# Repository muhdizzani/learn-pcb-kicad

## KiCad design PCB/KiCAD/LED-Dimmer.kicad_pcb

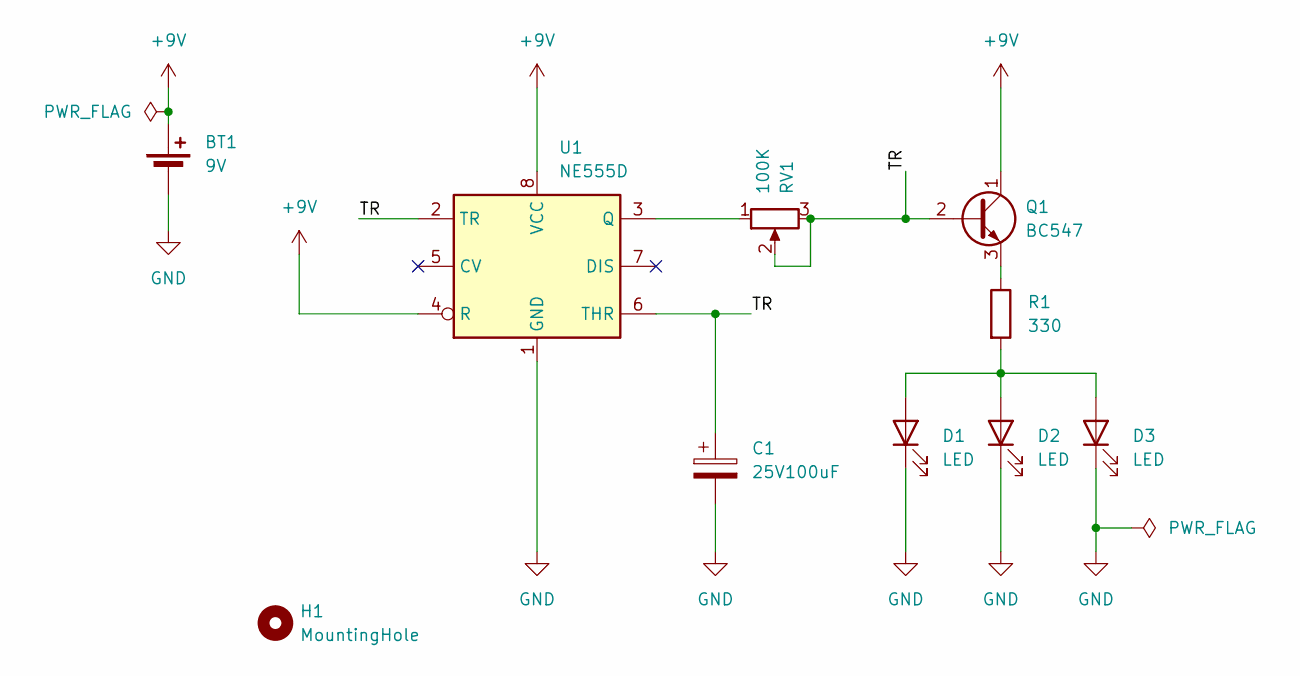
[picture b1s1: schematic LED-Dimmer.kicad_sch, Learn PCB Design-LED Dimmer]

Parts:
BT1: 9V; TerminalBlock_Phoenix_MKDS-1,5-2-5.08_1x02_P5.08mm_Horizont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
C1: 25V100uF; CP_Radial_D5.0mm_P2.00mm
D1, D2, D3: LED; LED_D5.0mm_Clear
H1: MountingHole; MountingHole_2.1mm
Q1: BC547; TO-92
R1: 330; R_Axial_DIN0204_L3.6mm_D1.6mm_P7.62mm_Horizontal
RV1: 100K; Potentiometer_Bourns_3296Y_Vertical
U1: NE555D; SOIC-8_3.9x4.9mm_P1.27mm

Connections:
+9V: BT1.1 (+), Q1.1 (C), U1.4 (R), U1.8 (VCC)
/TR: C1.1, Q1.2 (B), RV1.2, RV1.3, U1.2 (TR), U1.6 (THR)
GND: BT1.2 (-), C1.2, D1.1 (K), D2.1 (K), D3.1 (K), U1.1 (GND)
unnamed: D1.2 (A), D2.2 (A), D3.2 (A), R1.2
unnamed: Q1.3 (E), R1.1
unnamed: RV1.1, U1.3 (Q)

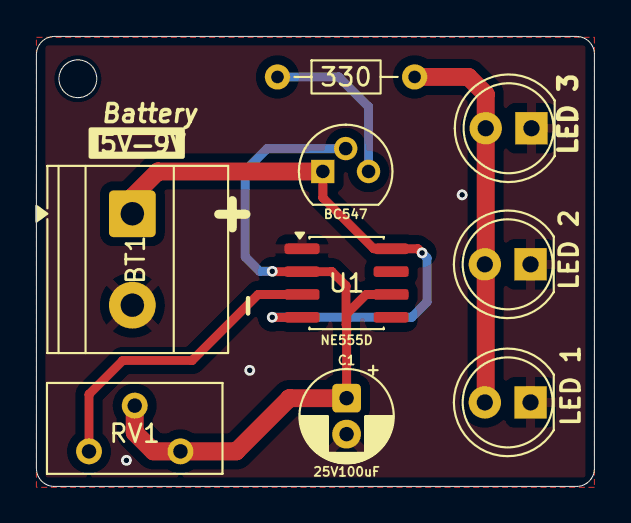
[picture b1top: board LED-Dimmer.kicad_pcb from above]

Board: 2 copper layers, 31.0 x 25.0 mm, 10 parts (0 on the bottom side), 6 nets.

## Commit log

2025-11-19 Generate Gerber
2025-11-19 Add PDF Schematic
2025-11-19 Revise layout
2025-11-19 Add new Gerber
2025-11-20 Add 330ohm resistor
2025-11-20 Add resistor
